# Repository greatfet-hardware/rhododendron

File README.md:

# GreatFET Rhododendron

This is very early progress of a High-Speed USB analysis neighbor for GreatFET. More details to come.

## PCB

Pictures by [Kate Temkin](https://twitter.com/ktemkin/status/1184521332832161792)

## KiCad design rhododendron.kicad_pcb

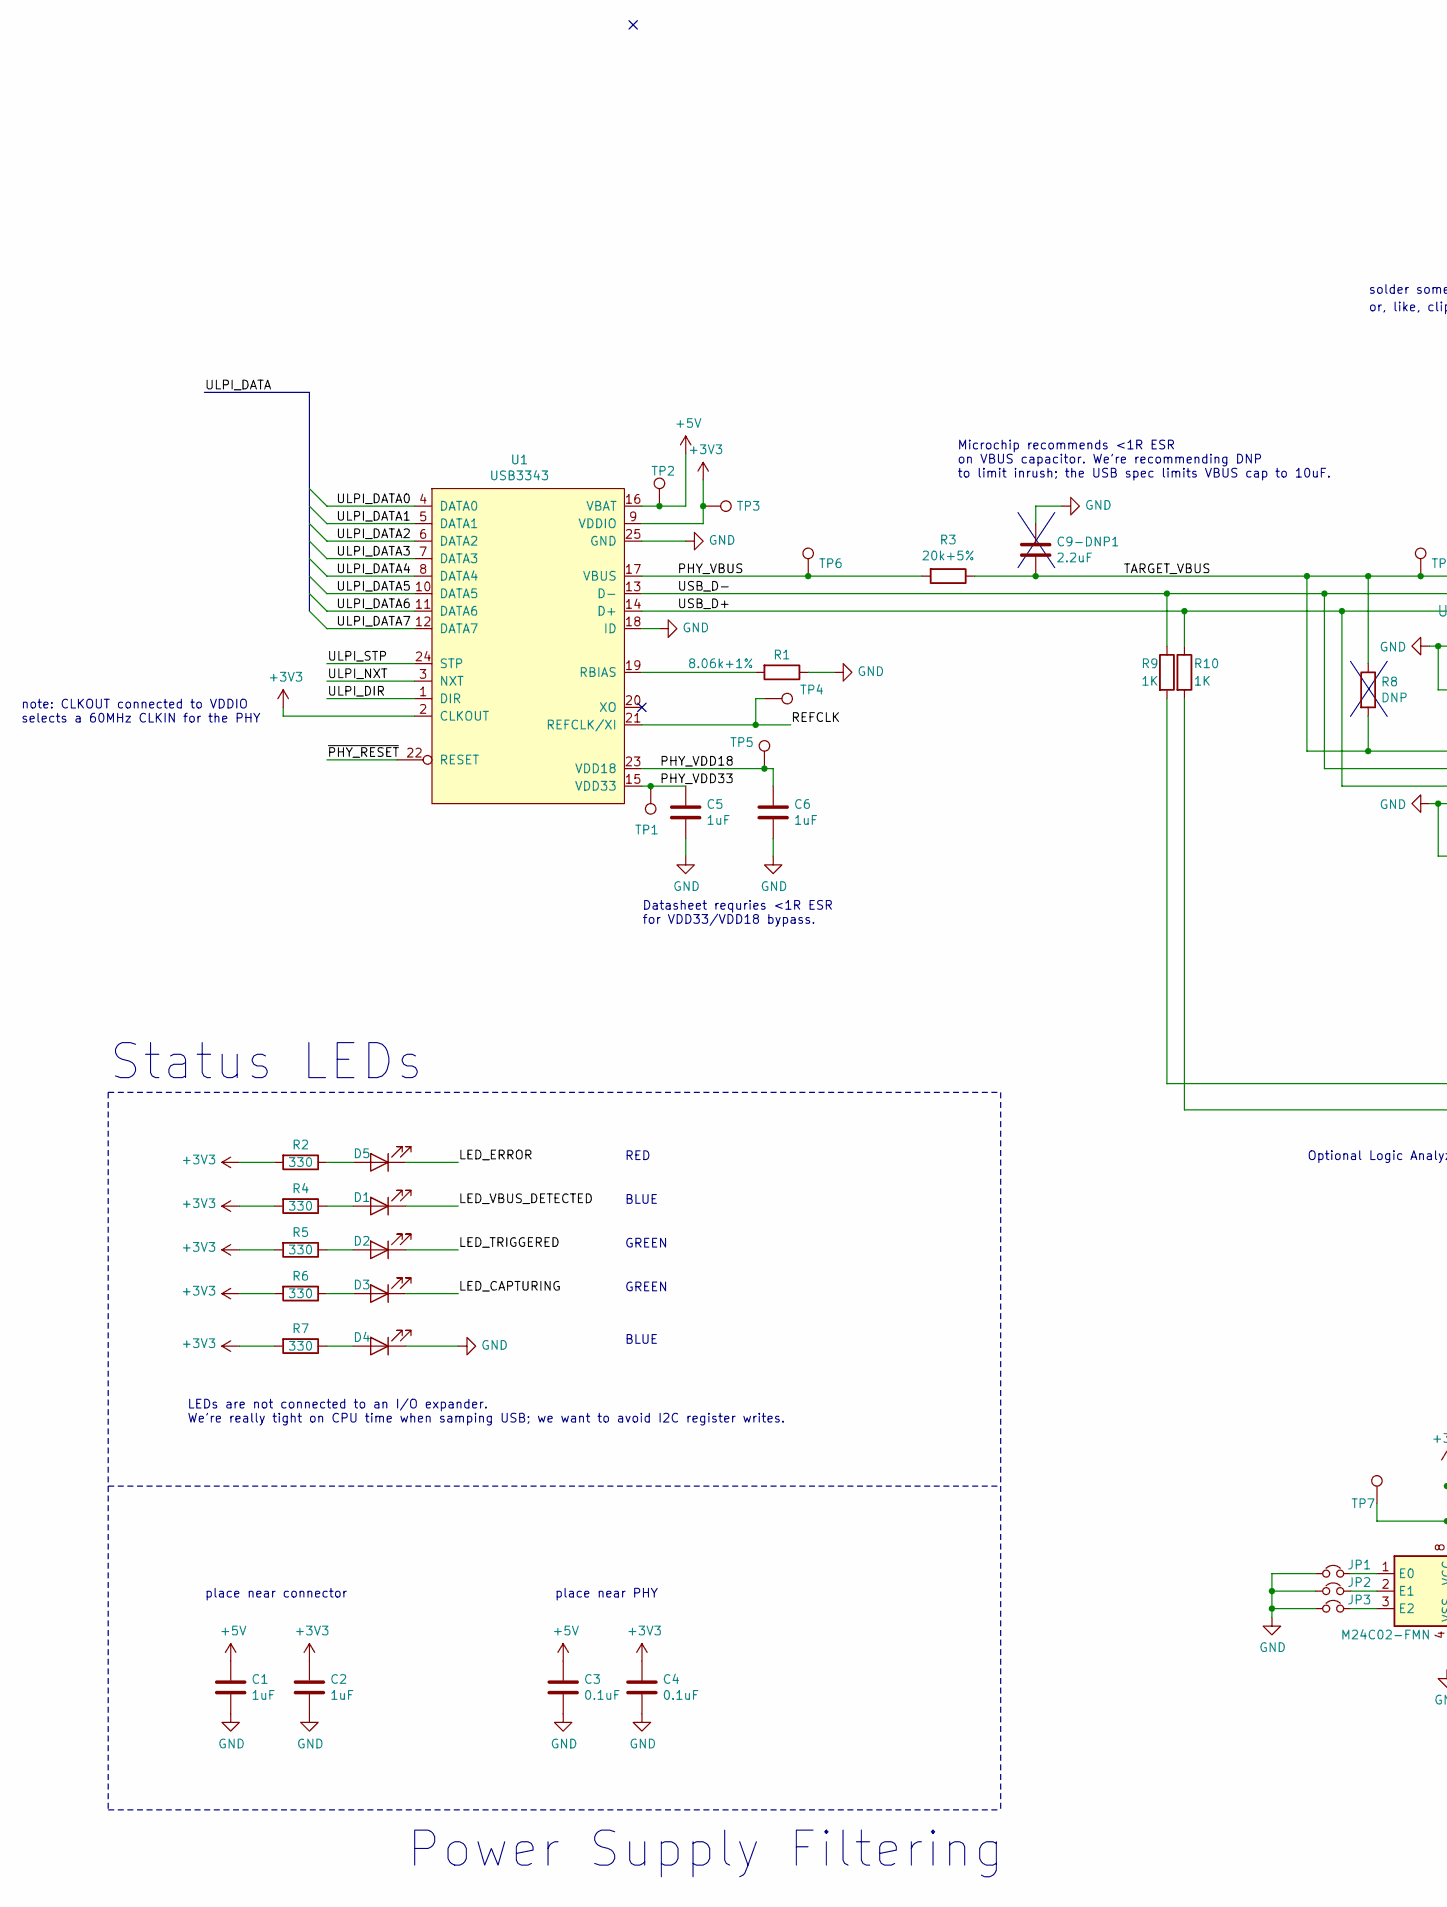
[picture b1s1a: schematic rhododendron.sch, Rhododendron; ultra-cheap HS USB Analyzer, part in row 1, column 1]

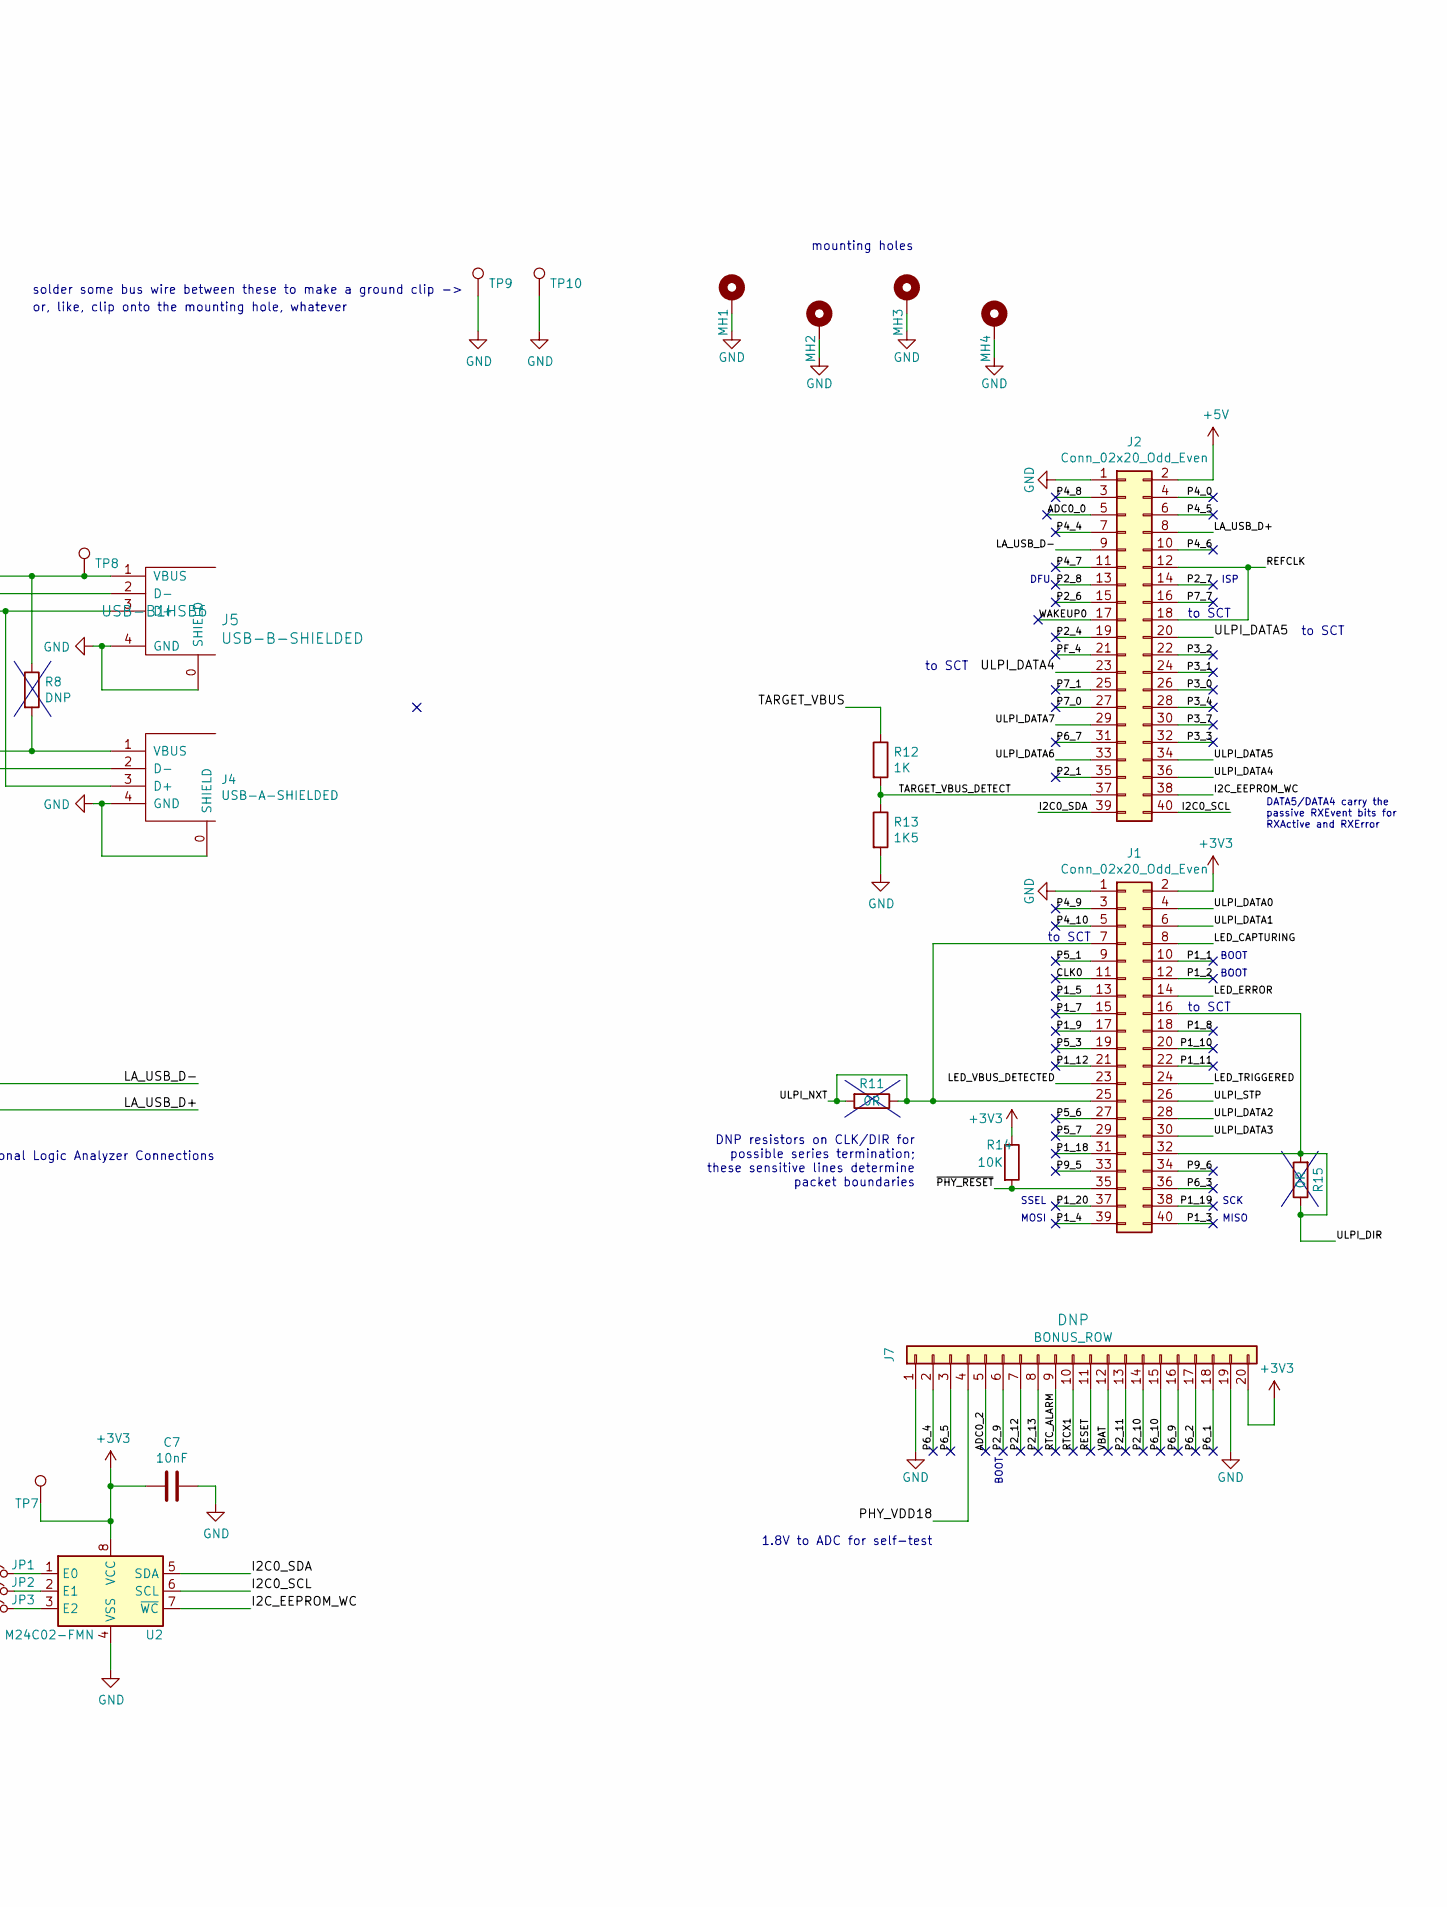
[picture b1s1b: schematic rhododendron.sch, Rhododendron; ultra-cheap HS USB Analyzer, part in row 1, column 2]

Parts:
C1, C2, C5, C6: 1uF; 0603
C3, C4: 0.1uF; 0603
C7: 10nF; 0603
C9-DNP1: 2.2uF; 0603
D1, D2, D3, D4, D5: LED; LED_0603_1608Metric_Pad1.05x0.95mm_HandSolder
J1, J2: Conn_02x20_Odd_Even; HEADER-2x20
J4: USB-A-SHIELDED; CONN-Amphenol-UE27AC54100; Manuf P/N UE27AC54100
J5: USB-B-SHIELDED; USB_B_OST_USB-_Horizontal
J7: BONUS_ROW; HEADER-1x20; Part Number SSQ-120-23-G-S
JP1, JP2, JP3: Jumper_NC_Small; 0402-SHORT-10MIL
MH1, MH2, MH3, MH4: MOUNTING_HOLE; HOLE126MIL-COPPER
R1: 8.06k+1%; 0603
R2, R4, R5, R6, R7: 330; 0603
R3: 20k+5%; 0603
R8: DNP; R_1206_3216Metric
R9, R10, R12: 1K; 0603
R11, R15: 0R; 0603
R13: 1K5; 0603
R14: 10K; 0603
TP1, TP2, TP3, TP4, TP5, TP6, TP7, TP8: TestPoint; TestPoint_Pad_D2.0mm
TP9, TP10: TestPoint; HEADER-1x1
U1: USB3343; VQFN-24-1EP_4x4mm_P0.5mm_EP2.45x2.45mm
U2: M24C02-FMN; SOIC-8_3.9x4.9mm_P1.27mm

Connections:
+3V3: C2.1, C4.1, C7.2, J1.2, J7.20, R2.2, R4.2, R5.2, R6.2, R7.2, R14.1, TP3.1, TP7.1, U1.2 (CLKOUT), U1.9 (VDDIO), U2.8 (VCC)
+5V: C1.1, C3.1, J2.2, TP2.1, U1.16 (VBAT)
/ADC0_0: J2.5
/ADC0_2: J7.5
/CLK0: J1.11
/I2C0_SCL: J2.40, U2.6 (SCL)
/I2C0_SDA: J2.39, U2.5 (SDA)
/I2C_EEPROM_WC: J2.38, U2.7 (~WC)
/LA_USB_D+: J2.8, R10.2
/LA_USB_D-: J2.9, R9.2
/LED_CAPTURING: D3.1 (K), J1.8
/LED_ERROR: D5.1 (K), J1.14
/LED_TRIGGERED: D2.1 (K), J1.24
/LED_VBUS_DETECTED: D1.1 (K), J1.23
/P1_1: J1.10
/P1_2: J1.12
/P1_3: J1.40
/P1_4: J1.39
/P1_5: J1.13
/P1_7: J1.15
/P1_8: J1.18
/P1_9: J1.17
/P1_10: J1.20
/P1_11: J1.22
/P1_12: J1.21
/P1_18: J1.31
/P1_19: J1.38
/P1_20: J1.37
/P2_1: J2.35
/P2_4: J2.19
/P2_6: J2.15
/P2_7: J2.14
/P2_8: J2.13
/P2_9: J7.6
/P2_10: J7.14
/P2_11: J7.13
/P2_12: J7.7
/P2_13: J7.8
/P3_0: J2.26
/P3_1: J2.24
/P3_2: J2.22
/P3_3: J2.32
/P3_4: J2.28
/P3_7: J2.30
/P4_0: J2.4
/P4_4: J2.7
/P4_5: J2.6
/P4_6: J2.10
/P4_7: J2.11
/P4_8: J2.3
/P4_9: J1.3
/P4_10: J1.5
/P5_1: J1.9
/P5_3: J1.19
/P5_6: J1.27
/P5_7: J1.29
/P6_1: J7.18
/P6_2: J7.17
/P6_3: J1.36
/P6_4: J7.2
/P6_5: J7.3
/P6_7: J2.31
/P6_9: J7.16
/P6_10: J7.15
/P7_0: J2.27
/P7_1: J2.25
/P7_7: J2.16
/P9_5: J1.33
/P9_6: J1.34
/PF_4: J2.21
/PHY_VBUS: R3.2, TP6.1, U1.17 (VBUS)
/PHY_VDD18: C6.1, J7.4, TP5.1, U1.23 (VDD18)
/PHY_VDD33: C5.2, TP1.1, U1.15 (VDD33)
/REFCLK: J2.12, J2.18, TP4.1, U1.21 (REFCLK/XI)
/RESET: J7.11
/RTCX1: J7.10
/RTC_ALARM: J7.9
/TARGET_VBUS: C9-DNP1.2, J4.1 (VBUS), J5.1 (VBUS), R3.1, R8.1, R8.2, R12.1, TP8.1
/TARGET_VBUS_DETECT: J2.37, R12.2, R13.1
/ULPI_DATA0: J1.4, U1.4 (DATA0)
/ULPI_DATA1: J1.6, U1.5 (DATA1)
/ULPI_DATA2: J1.28, U1.6 (DATA2)
/ULPI_DATA3: J1.30, U1.7 (DATA3)
/ULPI_DATA4: J2.23, J2.36, U1.8 (DATA4)
/ULPI_DATA5: J2.20, J2.34, U1.10 (DATA5)
/ULPI_DATA6: J2.33, U1.11 (DATA6)
/ULPI_DATA7: J2.29, U1.12 (DATA7)
/ULPI_DIR: J1.16, J1.32, R15.1, R15.2, U1.1 (DIR)
/ULPI_NXT: J1.7, J1.25, R11.1, R11.2, U1.3 (NXT)
/ULPI_STP: J1.26, U1.24 (STP)
/USB_D+: J4.3 (D+), J5.3 (D+), R10.1, U1.14 (D+)
/USB_D-: J4.2 (D-), J5.2 (D-), R9.1, U1.13 (D-)
/VBAT: J7.12
/WAKEUP0: J2.17
/~PHY_RESET: J1.35, R14.2, U1.22 (RESET)
GND: C1.2, C2.2, C3.2, C4.2, C5.1, C6.2, C7.1, C9-DNP1.1, D4.1 (K), J1.1, J2.1, J4.0 (SHIELD), J4.4 (GND), J5.0 (SHIELD), J5.4 (GND), J7.1, J7.19, JP1.1, JP2.1, JP3.1, MH1.1, MH2.1, MH3.1, MH4.1, R1.1, R13.2, TP9.1, TP10.1, U1.18 (ID), U1.25 (GND), U2.4 (VSS)
unnamed: D1.2 (A), R4.1
unnamed: D2.2 (A), R5.1
unnamed: D3.2 (A), R6.1
unnamed: D4.2 (A), R7.1
unnamed: D5.2 (A), R2.1
unnamed: JP1.2, U2.1 (E0)
unnamed: JP2.2, U2.2 (E1)
unnamed: JP3.2, U2.3 (E2)
unnamed: R1.2, U1.19 (RBIAS)

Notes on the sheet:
BOOT
Datasheet requries <1R ESR for VDD33/VDD18 bypass.
Microchip recommends <1R ESR on VBUS capacitor. We're recommending DNP to limit inrush; the USB spec limits VBUS cap to 10uF.
LEDs are not connected to an I/O expander. We're really tight on CPU time when samping USB; we want to avoid I2C register writes.
Optional Logic Analyzer Connections
DFU
SSEL
SCK
MOSI
MISO
Status LEDs
Power Supply Filtering
place near connector
place near PHY
solder some bus wire between these to make a ground clip ->
or, like, clip onto the mounting hole, whatever
mounting holes
note: CLKOUT connected to VDDIO selects a 60MHz CLKIN for the PHY
ISP
1.8V to ADC for self-test
RED
BLUE
GREEN
DATA5/DATA4 carry the passive RXEvent bits for RXActive and RXError
to SCT
DNP resistors on CLK/DIR for possible series termination; these sensitive lines determine packet boundaries

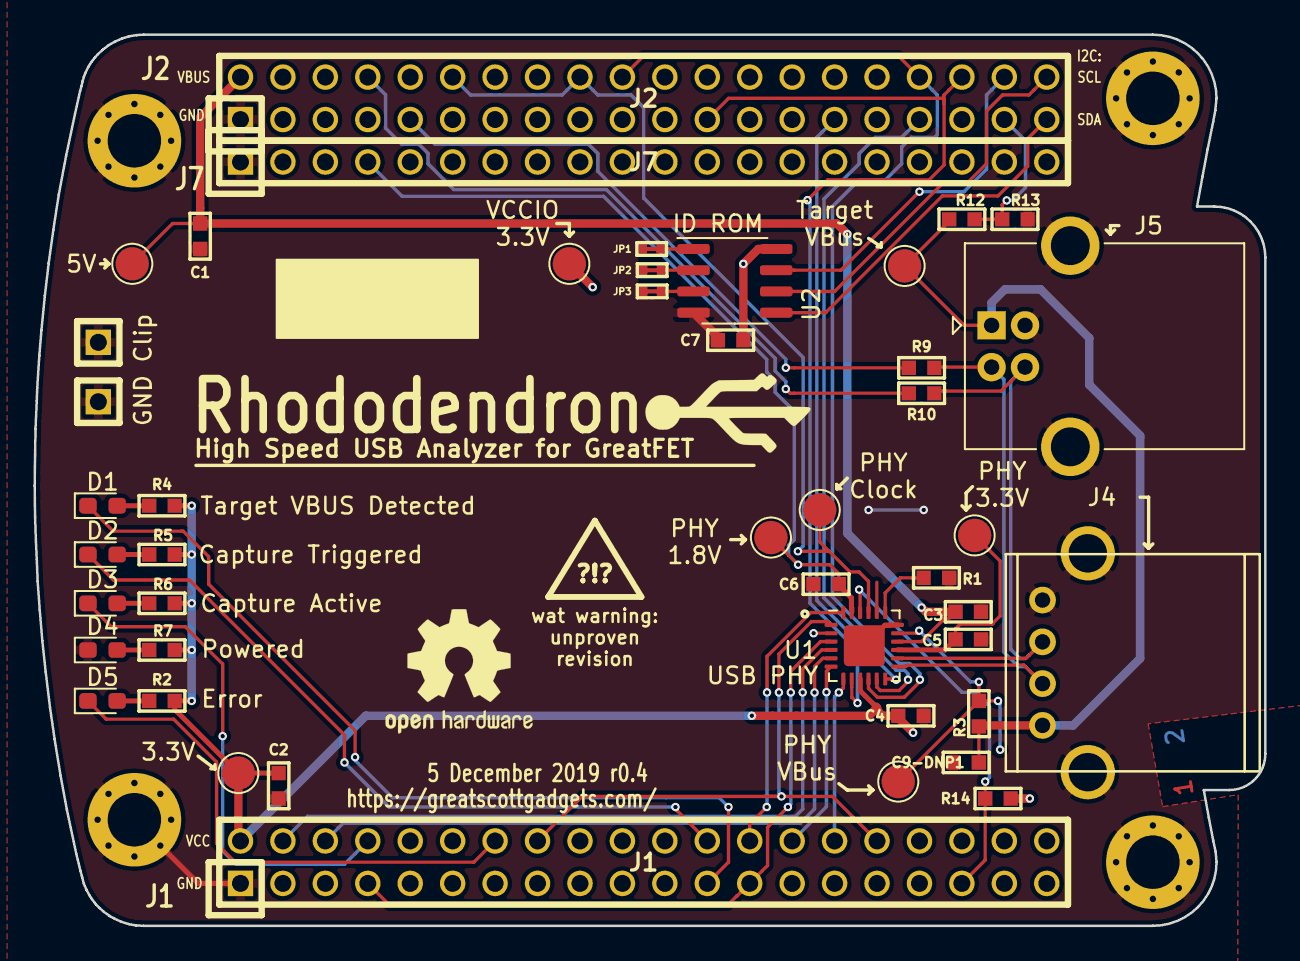
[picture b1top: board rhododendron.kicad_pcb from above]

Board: 2 copper layers, 73.7 x 53.3 mm, 50 parts (1 on the bottom side), 41 nets.

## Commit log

2019-05-02 initial commit of r0 Rhodadendon schematic
2019-05-08 fix my inability to spell rhododendron :)
2019-07-16 rhododendron: capture r0.2
2019-07-17 r0.2: finalize for ordering; improve silkscreen; minor tweaks
2019-07-17 spelling is still hard
2019-10-16 r0.3: capture schematic with all changes
2019-10-16 r0.3: route the changes made in the r0.3 schematic
2019-10-16 r0.3: add 3d models and prepare for plotting
2019-10-16 r0.3: round the corners on the support ledge
2019-12-05 r0.4: correct two "wasted" header pins (incorrectly connected to 3V3)
2020-07-03 adopt OSHWA convention for SPI signal names https://www.oshwa.org/a-resolution-to-redefine-spi-signal-names
2022-03-04 BOM: Fix unclosed quotes in Bill of material CSV
2022-03-04 BOM: Normalize rows, now renders fine
2022-03-04 Add pcb images from @ktemkin
2022-03-05 BOM: Extend with some part numbers/datasheet
2022-03-07 BOM: Sync with current schematics (r0.4 - commit: 2398f33)

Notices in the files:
rhododendron.sch:
Copyright 2019 Great Scott Gadgets
License: BSD-3-Clause
